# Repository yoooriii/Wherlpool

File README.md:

# Wherlpool
Whirlpool refrigerator Arduino ATmega8 circuit board and code project.

It features DS1302 timekeeping chip.
Arduino Library: Copyright (c) 2009, Matt Sparks (2-clause BSD license).
[DS1302 RTC library for Arduino](https://github.com/msparks/arduino-ds1302)

About this project:
It contains all documents to assemble and program a circuit board for
a Whirlpool refrigerator, or any other refrigerator with a few (or none) modifications.
It consists of 2 projects:
+ Eagle CAD circuit board
+ Arduino based firmware (ATmega8)

### PCB signal connections:

```
[Signal name]           : [pin] : [direction]
CP = control panel      : ----------
CP Reset button         : PD3   : in
CP +/- (up/dn) button   : PD4   : in
CP Led1                 : PC3   : out
CP Led2                 : PC4   : out
CP Led3                 : PC5   : out
MB = main board         : ----------
Defrost sensor          : ADC6  : in
Freezer sensor          : ADC7  : in
Door open sw            : PD2   : in
Fan 12V                 : PB1   : out
Motor                   : PB0   : out
Defrost heater          : PD5   : out
```

Other things:

In the freezer compartment I am using 2x 12V fans taken from used ATX power supply units.
One blows in the freezer and another blows from the freezer to the main compartment (+5C).
They work quite well, the only thing to consider is, as soon as fans work at low temperature 
I had to use full synthetic low temperature oil (Nissan 5w30 motor oil in my case). Before that they worked well
up to -5 -10 Celsius, but at -20 ... -30 Celsius they became too noisy and I had to oil them.

TODO:
defrost timer.
It is not implemented yet.
Logic: once each 1-2 days the fridge must be defrozen.
1. turn the compressor off and 
2. turn the heater on for 15-20 (30) minutes.
Additionally: save the last successful heating time. Note: electricity may go off so I should keep settings in DS1302 RAM.
(For some reason ATmega8 eerprom gets corrupted in my case, looks like sporadic code executed when power goes down)

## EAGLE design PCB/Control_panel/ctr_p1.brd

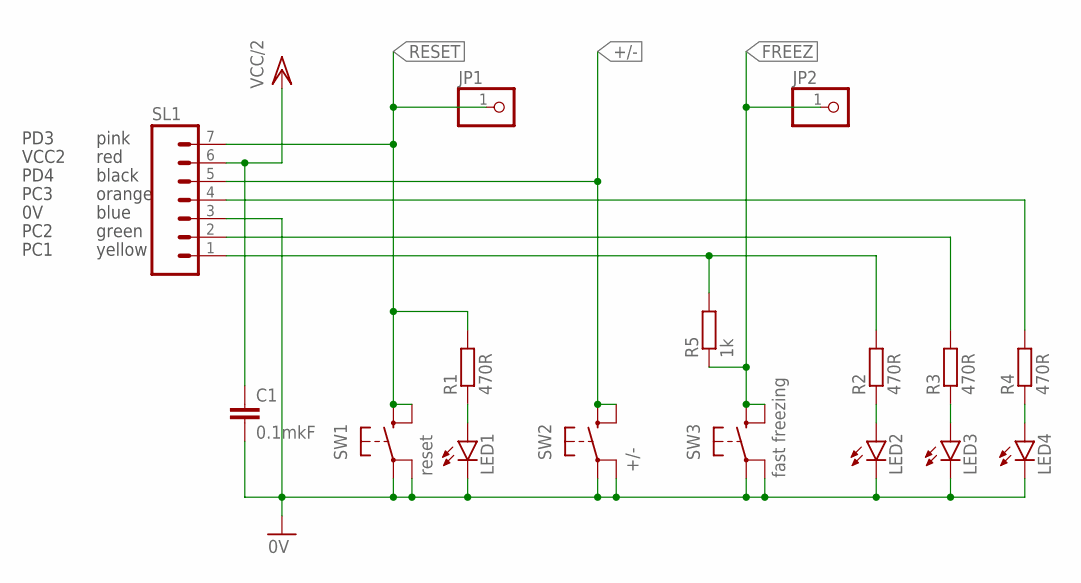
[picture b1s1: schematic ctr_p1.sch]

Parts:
C1: 0.1mkF; C3225
JP1, JP2: PINHD-1X1; 1X01
LED1, LED2, LED3, LED4: LED3MM
R1, R2, R3, R4: 470R; R0805
R5: 1k; R0805
SL1: MA07; 07PA
SW1: reset; SWITCH
SW2: +/-; SWITCH
SW3: fast freezing; SWITCH

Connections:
0V: C1.2, LED1.K (C), LED2.K (C), LED3.K (C), LED4.K (C), SL1.3, SW1.P$1A, SW1.P$2A (P1), SW2.P$1A, SW2.P$2A (P1), SW3.P$1A, SW3.P$2A (P1)
+/-: SL1.5, SW2.P$1B (S), SW2.P$2B (S1)
FREEZ: JP2.1, R5.1, SW3.P$1B (S), SW3.P$2B (S1)
unnamed: LED2.A, R2.1
unnamed: LED3.A, R3.1
unnamed: LED4.A, R4.1
unnamed: R2.2, R5.2, SL1.1
unnamed: R3.2, SL1.2
unnamed: R4.2, SL1.4
unnamed: LED1.A, R1.1
RESET: JP1.1, R1.2, SL1.7, SW1.P$1B (S), SW1.P$2B (S1)
VCC/2: C1.1, SL1.6

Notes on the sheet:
yellow
green
blue
orange
black
red
pink
PD3
PD4
PC1
PC2
PC3
VCC2

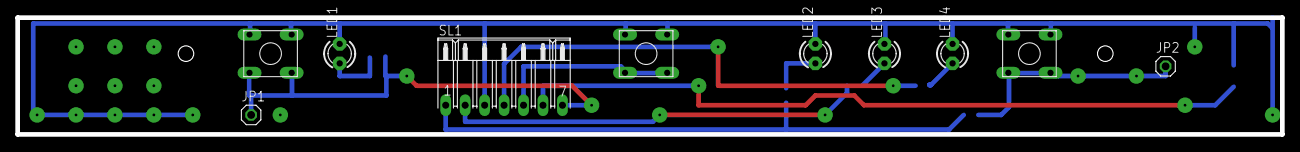
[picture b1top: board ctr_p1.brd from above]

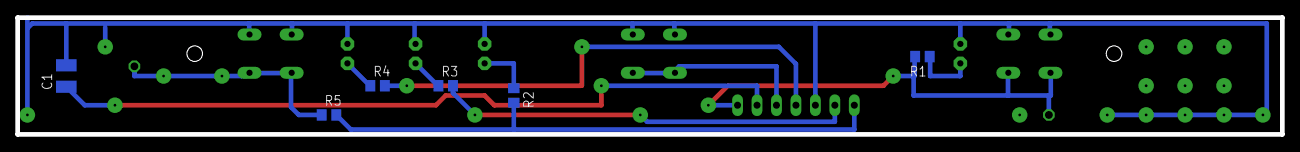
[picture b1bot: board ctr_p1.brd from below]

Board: 2 copper layers, 165.1 x 15.2 mm, 16 parts (6 on the bottom side), 12 nets.

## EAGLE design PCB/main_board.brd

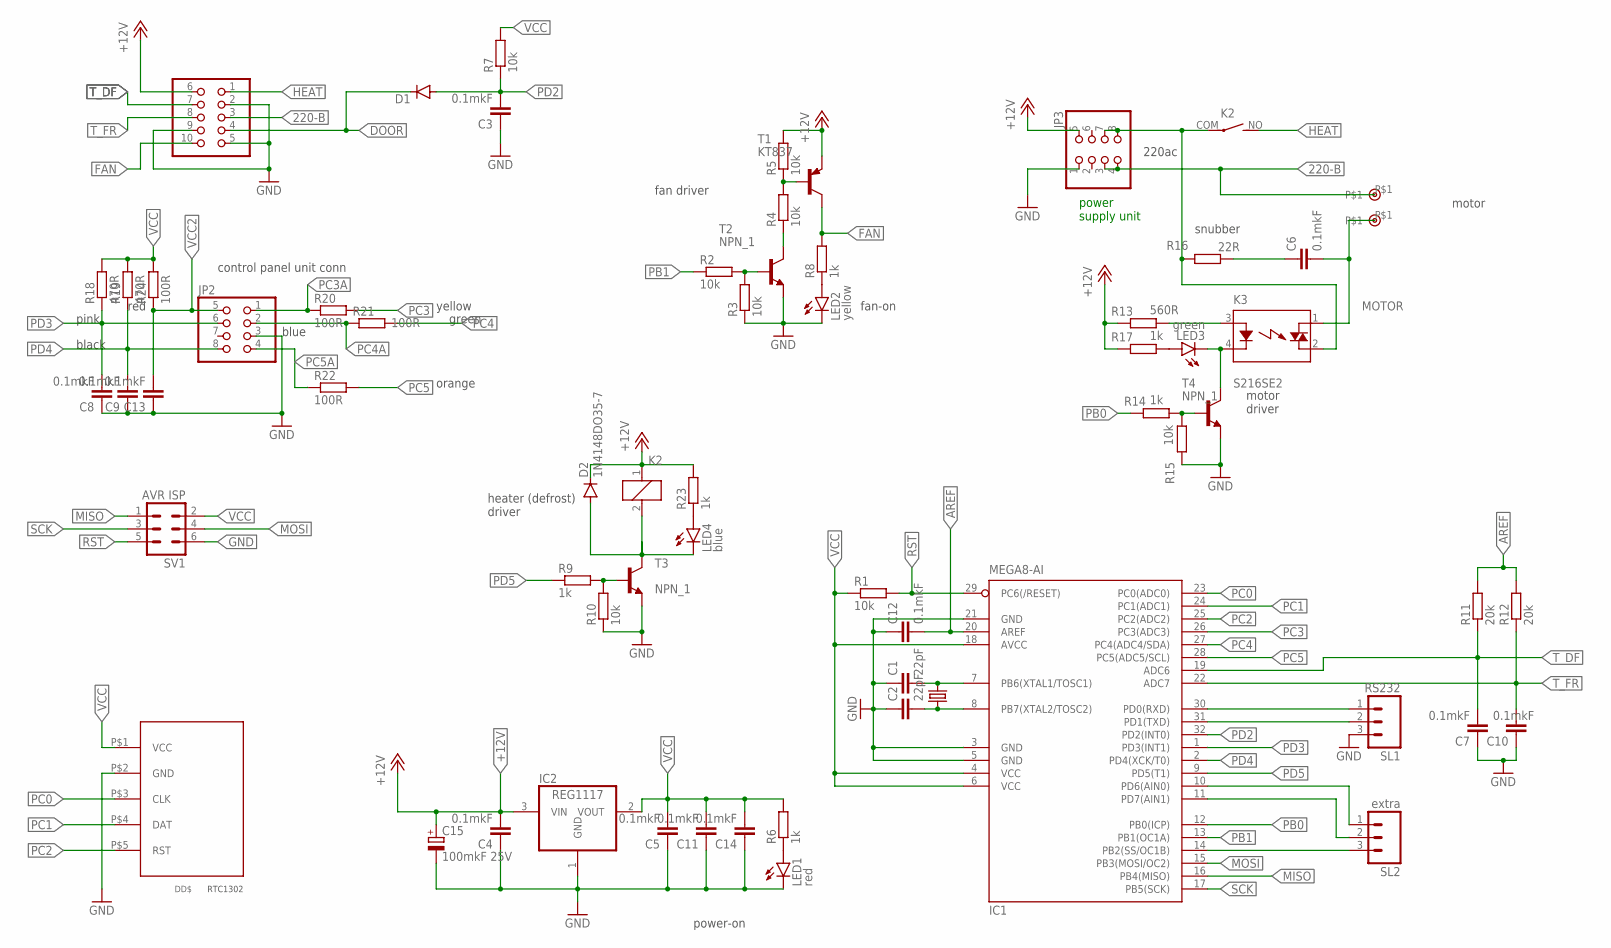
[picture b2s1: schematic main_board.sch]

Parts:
C1, C2: 22pF; C0402K
C3, C5, C7, C8, C9, C10, C11, C12, C13, C14: 0.1mkF; C0805K
C4: 0.1mkF; C5B2.5
C6: 0.1mkF; PACK_2PIN_150
C15: 100mkF 25V; B45181A
CN1, CN2: CONTACT
D1, D2: 1N4148DO35-7; DO35-7
DD1: RTC-DS1302-MODULEABOVE; RTC-DS1302-M2
IC1: MEGA8-AI; TQFP32-08
IC2: REG1117; SOT223
JP1: CONN_2X5_4.2MMANGLE-0; CONN_2X05_4.2MM
JP2, JP3: CONN_2X4_4.2MM; CONN_2X04_4.2MM
K2: RELAY_ALK3213; ALK3213
K3: S216SE2; S2XXEX
LED1: red; LED3MM
LED2: yellow; LED3MM
LED3: green; LED3MM
LED4: blue; LED3MM
R1, R2, R3, R4, R5, R7, R10, R15: 10k; R0805
R6, R8, R9, R14, R17, R23: 1k; R0805
R11, R12: 20k; R0805
R13: 560R; R0805
R16: 22R; PACK_2PIN_150
R18, R19: 470R; R0805
R20, R21, R22, R24: 100R; R0805
SL1: RS232; 03P
SL2: extra; 03P
SV1: AVR ISP; MA03-2
T1: KT837; TO220V
T2, T3, T4: NPN_1; TO92
X1: 16MHz; HC49

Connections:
220-A: JP3.7, JP3.8, K2.COM, K3.2 (DS2), R16.P$2 (2)
220-B: CN1.P$1, JP1.3, JP3.3, JP3.4
+12V: C4.2, C15.+, D2.C, IC2.3 (VIN), JP1.6, JP3.5, K2.1, R5.2, R13.1, R17.1, R23.2, T1.3 (E)
AREF: C12.2, IC1.20 (AREF), R11.2, R12.2
DOOR: D1.C, JP1.4
FAN: JP1.10, R8.2, T1.2 (C)
GND: C1.1, C2.1, C3.1, C4.1, C5.1, C7.1, C8.1, C9.1, C10.1, C11.1, C12.1, C13.1, C14.1, C15.-, DD1.P$2 (GND), IC1.3 (GND), IC1.5 (GND), IC1.21 (GND), IC2.1 (GND), JP1.2, JP1.5, JP1.9, JP2.3, JP3.1, LED1.K (C), LED2.K (C), R3.1, R10.1, R15.1, SL1.3, SV1.6, T2.E, T3.E, T4.E
HEAT: JP1.1, K2.NO (S)
MISO: IC1.16 (PB4(MISO)), SV1.1
MOSI: IC1.15 (PB3(MOSI/OC2)), SV1.4
MOTOR: C6.P$2 (2), CN2.P$1, K3.1 (DS1)
unnamed: C6.P$1 (1), R16.P$1 (1)
unnamed: R9.2, R10.2, T3.B
unnamed: R2.2, R3.2, T2.B
unnamed: R4.1, T2.C
unnamed: R4.2, R5.1, T1.1 (B)
unnamed: LED1.A, R6.1
unnamed: IC1.30 (PD0(RXD)), SL1.1
unnamed: LED2.A, R8.1
unnamed: IC1.31 (PD1(TXD)), SL1.2
unnamed: K3.3 (A), R13.2
unnamed: R14.2, R15.2, T4.B
unnamed: K3.4 (K), LED3.K (C), T4.C
unnamed: LED3.A, R17.2
unnamed: IC1.10 (PD6(AIN0)), SL2.1
unnamed: IC1.11 (PD7(AIN1)), SL2.2
unnamed: IC1.14 (PB2(SS/OC1B)), SL2.3
unnamed: LED4.A, R23.1
unnamed: D2.A, K2.2, LED4.K (C), T3.C
PB0: IC1.12 (PB0(ICP)), R14.1
PB1: IC1.13 (PB1(OC1A)), R2.1
PC0: DD1.P$3 (CLK), IC1.23 (PC0(ADC0))
PC1: DD1.P$4 (DAT), IC1.24 (PC1(ADC1))
PC2: DD1.P$5 (RST), IC1.25 (PC2(ADC2))
PC3: IC1.26 (PC3(ADC3)), R20.2
PC3A: JP2.1, R20.1
PC4: IC1.27 (PC4(ADC4/SDA)), R21.2
PC4A: JP2.2, R21.1
PC5: IC1.28 (PC5(ADC5/SCL)), R22.2
PC5A: JP2.4, R22.1
PD2: C3.2, D1.A, IC1.32 (PD2(INT0)), R7.1
PD3: C8.2, IC1.1 (PD3(INT1)), JP2.6, R18.1
PD4: C9.2, IC1.2 (PD4(XCK/T0)), JP2.8, R19.1
PD5: IC1.9 (PD5(T1)), R9.1
RST: IC1.29 (PC6(/RESET)), R1.2, SV1.5
SCK: IC1.17 (PB5(SCK)), SV1.3
T_DF: C7.2, IC1.19 (ADC6), JP1.7, R11.1
T_FR: C10.2, IC1.22 (ADC7), JP1.8, R12.1
VCC: C5.2, C11.2, C14.2, DD1.P$1 (VCC), IC1.4 (VCC), IC1.6 (VCC), IC1.18 (AVCC), IC2.2 (VOUT), R1.1, R6.2, R7.2, R18.2, R19.2, R24.2, SV1.2
VCC2: C13.2, JP2.5, R24.1
XTAL1: C1.2, IC1.7 (PB6(XTAL1/TOSC1)), X1.2
XTAL2: C2.2, IC1.8 (PB7(XTAL2/TOSC2)), X1.1

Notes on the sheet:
power-on
fan-on
heater (defrost) driver
220ac
motor
motor driver
snubber
blue
orange
yellow
green
red
pink
black
control panel unit conn
fan driver
power supply unit

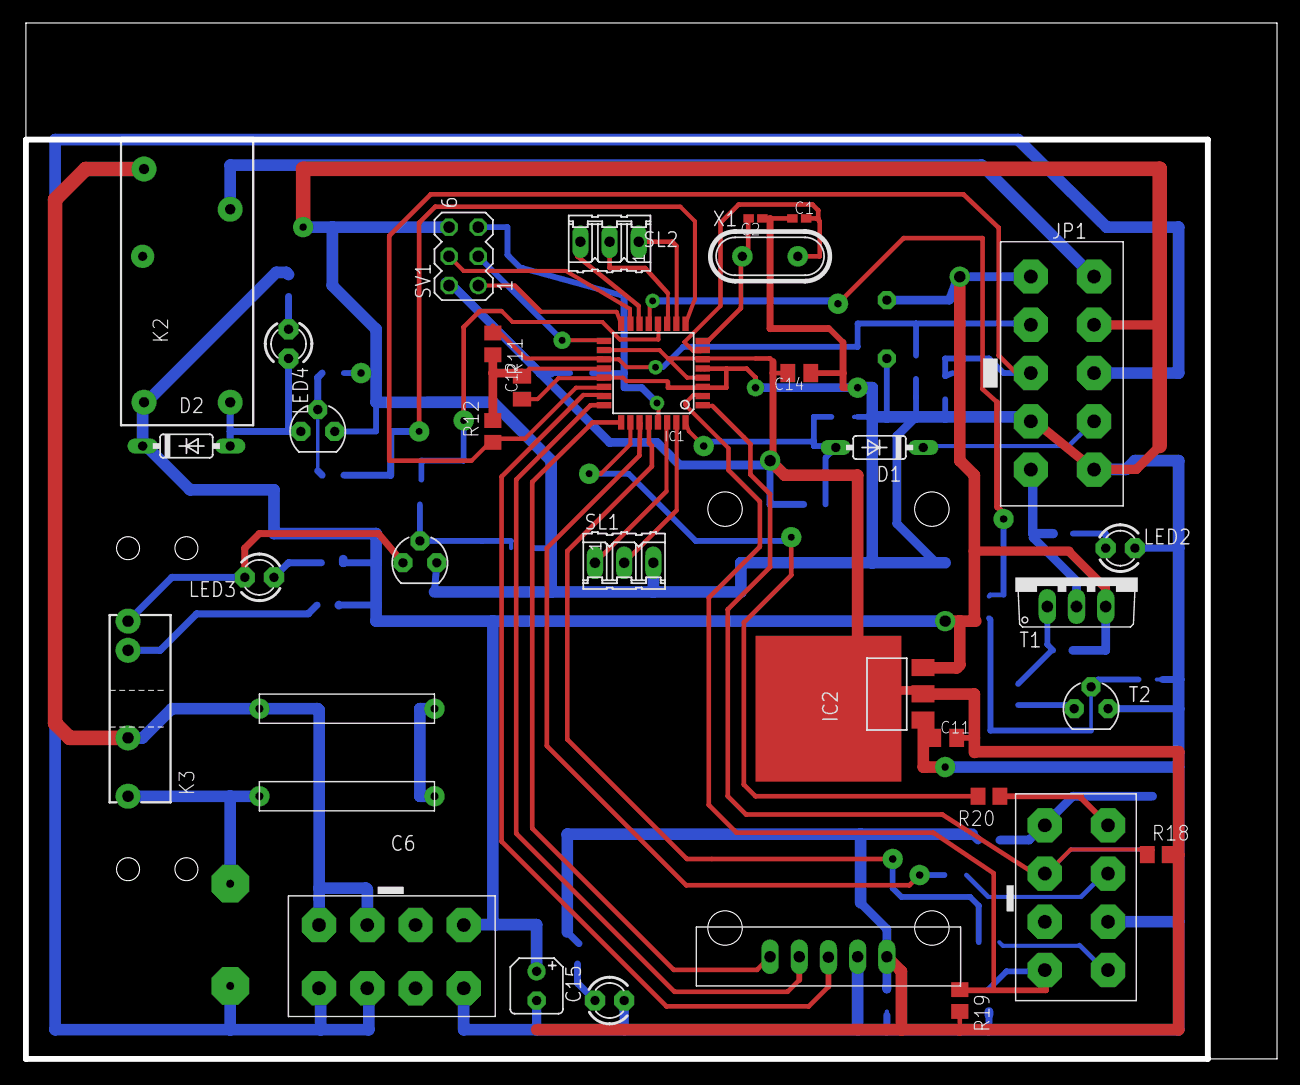
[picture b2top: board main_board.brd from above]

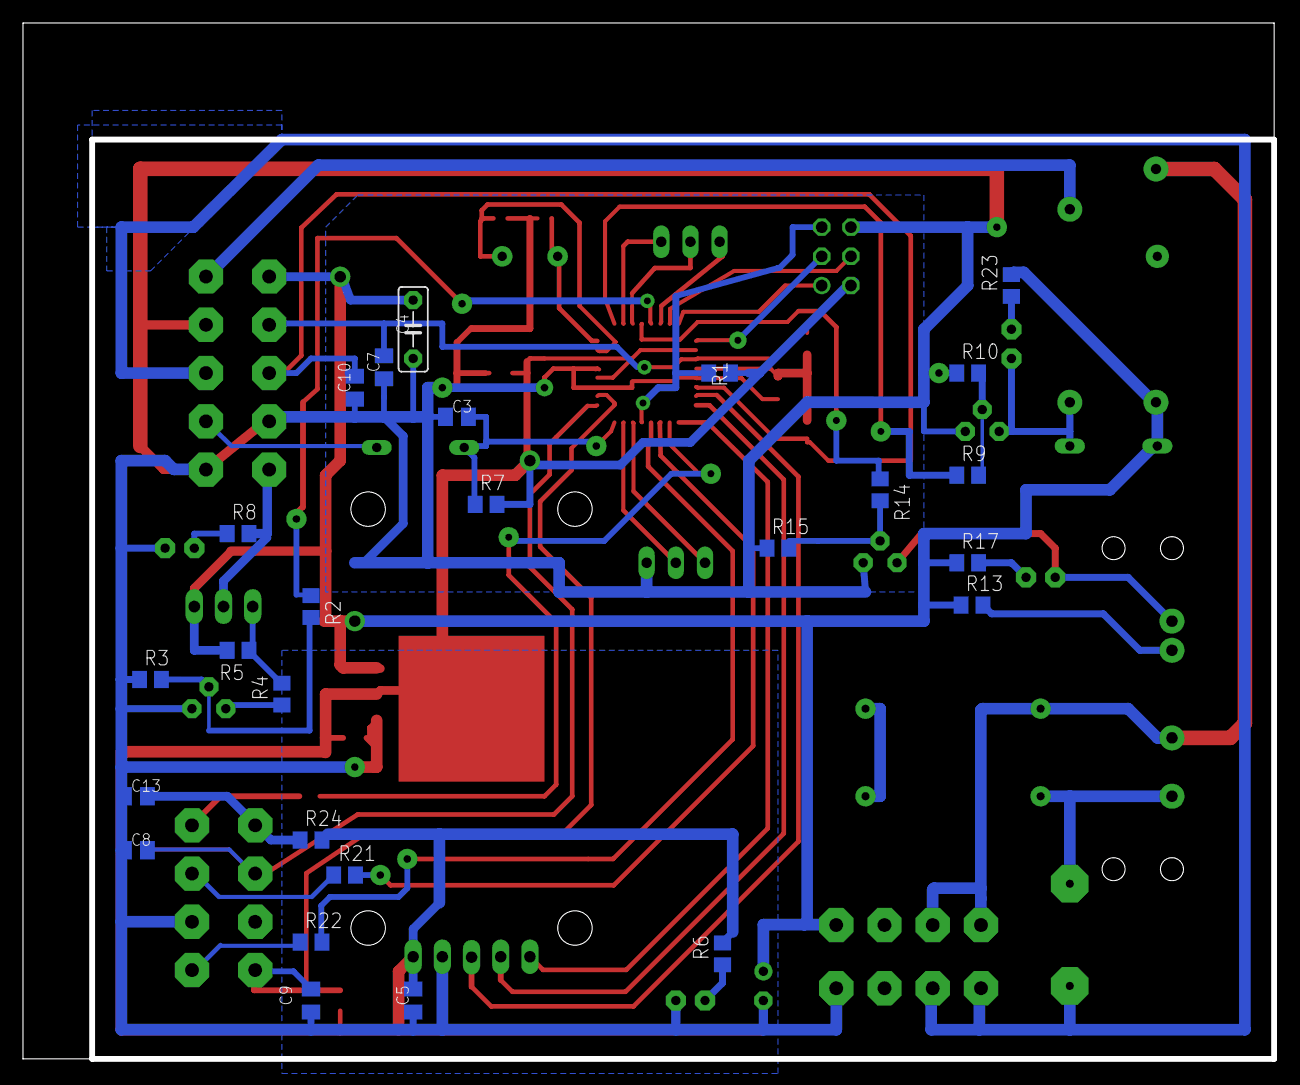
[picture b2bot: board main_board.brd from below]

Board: 2 copper layers, 108.9 x 90.2 mm, 63 parts (26 on the bottom side), 52 nets.

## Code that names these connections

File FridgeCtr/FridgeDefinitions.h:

// FridgeDefinitions.h
// Wherlpool

#include <pins_arduino.h>

#ifndef _FRIDGE_DEFINITIONS_
#define _FRIDGE_DEFINITIONS_

#define pp_Fan (PIN_PB1)
#define pp_Motor (PIN_PB0)
#define pp_Heater (PIN_PD5)

// defrost sensor, analog input
#define pp_TDF (PIN_A6)
// thermo sensor, analog input
#define pp_Thermo (PIN_A7)
#define pp_Door (PIN_PD2)

// reset button
#define pp_Reset (PIN_PD3)
// +/- (up/down) button
#define pp_UpDn (PIN_PD4)
// 3 temperature mode leds
#define pp_Led1 (PIN_PC3)
#define pp_Led2 (PIN_PC4)
#define pp_Led3 (PIN_PC5)

// heat time in minutes
#define HeatTime (15)

#endif

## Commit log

2023-03-10 add project description to readme file
2023-03-10 add Eagle PCB project
2023-03-10 add Arduino firmware project
2023-03-10 add pictures
2023-03-10 add detailed description
